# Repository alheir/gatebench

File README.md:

# GateBench

Educational FPGA lab board for the UPduino v3.1. Switches, LEDs, 7-segment display, VGA, R-2R DAC, ADC and WS2812 behind shift-register scan chains, with a Verilog BSP and worked examples.

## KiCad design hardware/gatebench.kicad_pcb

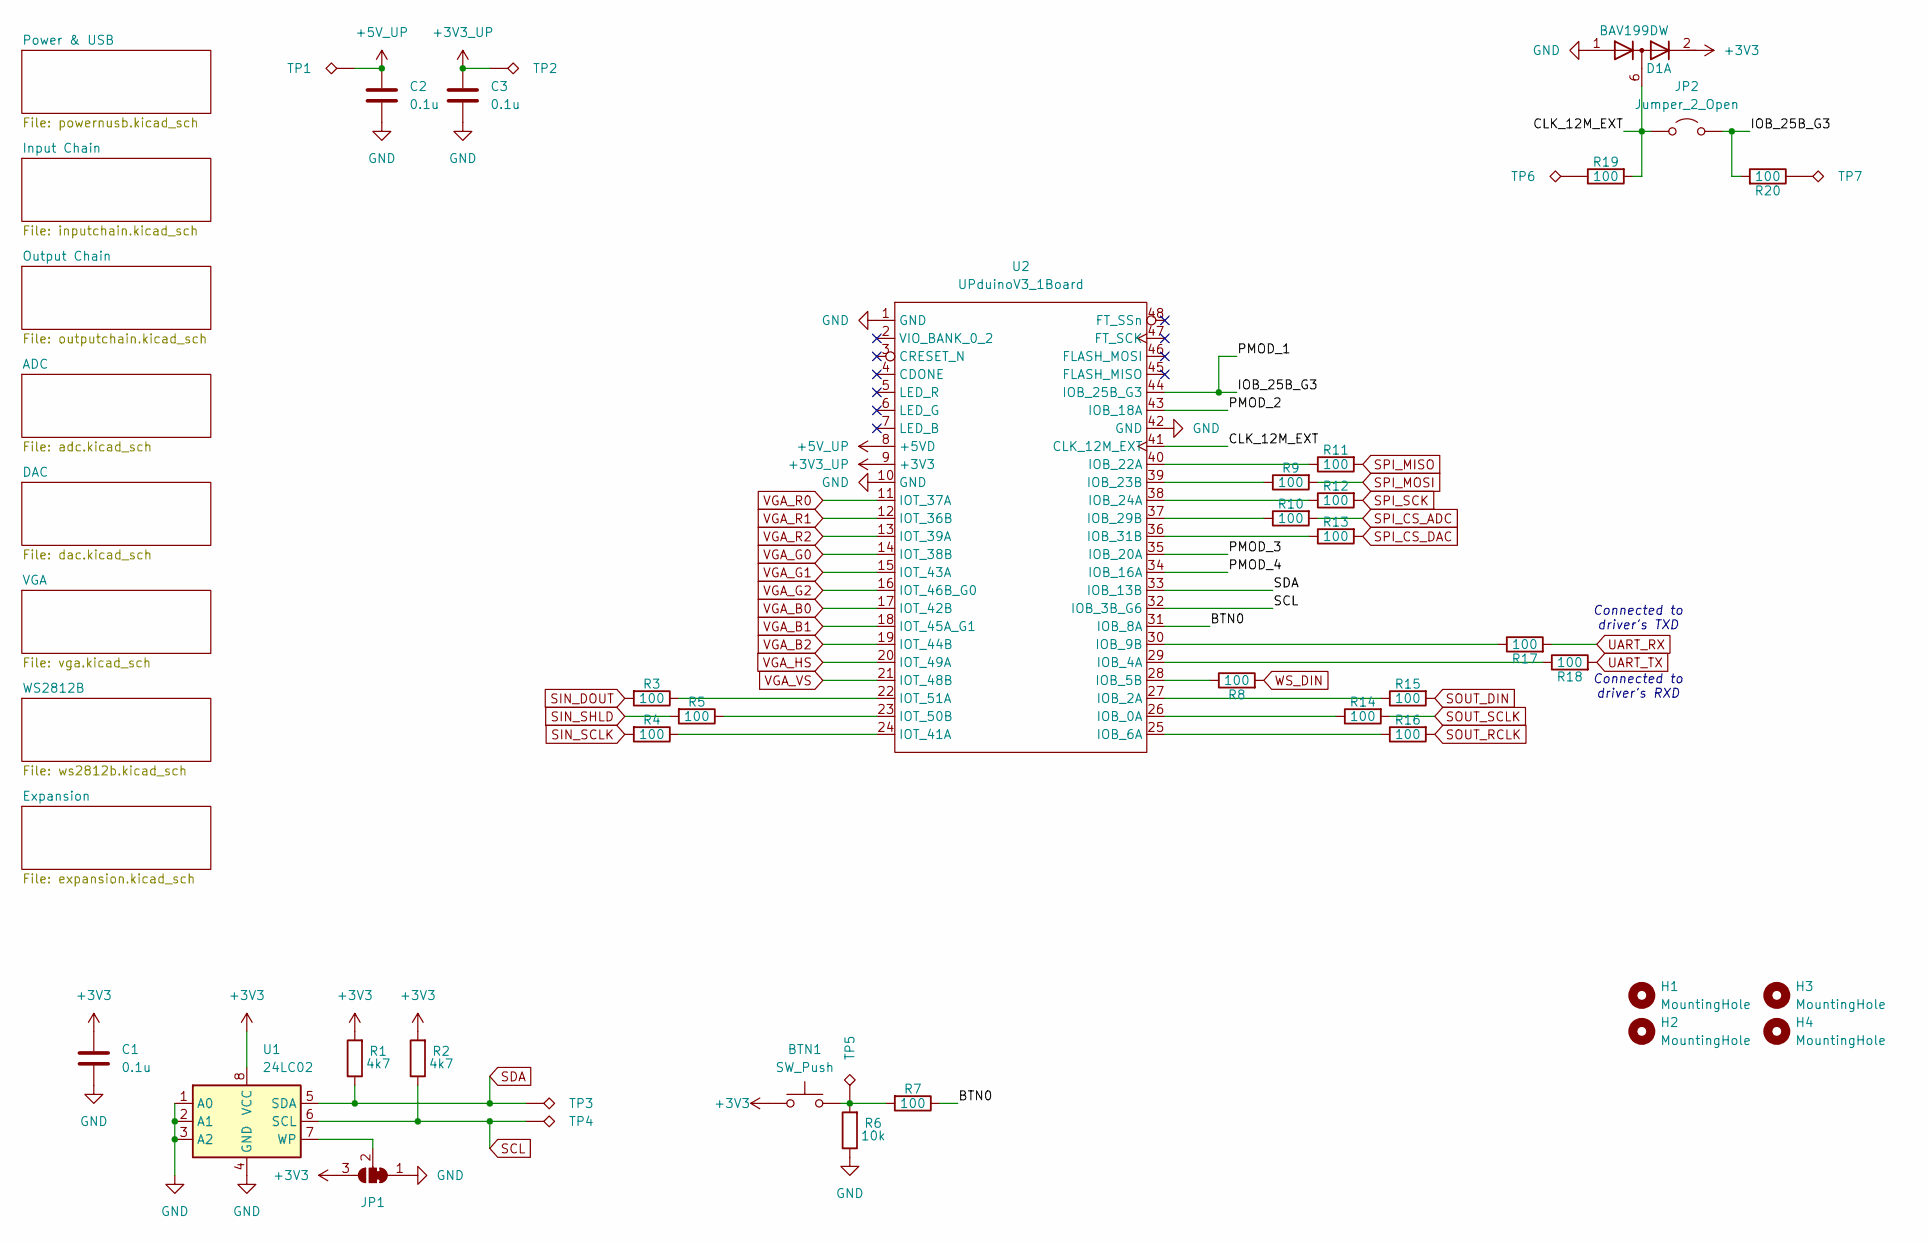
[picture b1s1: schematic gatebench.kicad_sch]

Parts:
BTN1: SW_Push; SW_PUSH_6mm_H8.5mm; JLCPCB C22397158
C1, C2, C3: 0.1u; C_0603_1608Metric_Pad1.08x0.95mm_HandSolder; JLCPCB C1705
D1: BAV199DW; SOT-363_SC-70-6
H1, H2, H3, H4: MountingHole; MountingHole_3.2mm_M3
JP1: SolderJumper_3_Bridged12; SolderJumper-3_P1.3mm_Bridged2Bar12_RoundedPad1.0x1.5mm_Num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
JP2: Jumper_2_Open
R1, R2: 4k7; R_0603_1608Metric; JLCPCB C22356621
R3, R4, R5, R7, R8, R9, R10, R11, R12, R13, R14, R15, R16, R17, R18, R19, R20: 100; R_0603_1608Metric; JLCPCB C22356621
R6: 10k; R_0603_1608Metric; JLCPCB C22356621
TP1, TP2, TP3, TP4, TP5, TP6, TP7: TestPoint_Alt; PinHeader_1x01_P2.54mm_Vertical
U1: 24LC02; SOIC-8_3.9x4.9mm_P1.27mm
U2: UPduinoV3_1Board; upduino_v3_1

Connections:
+3V3: BTN1.1, C1.1, D1.2 (K2), JP1.3 (B), R1.2, R2.2, U1.8 (VCC); also elsewhere on the board
+3V3_UP: C3.1, TP2.1 (1_1), U2.9 (+3V3); also elsewhere on the board
+5V_UP: C2.1, TP1.1 (1_1), U2.8 (+5VD); also elsewhere on the board
/BTN0: R7.1, U2.31 (IOB_8A)
/CLK_12M_EXT: D1.6 (K3A4), JP2.1 (A), R19.2, U2.41 (CLK_12M_EXT)
/IOB_25B_G3: JP2.2 (B), R20.2, U2.44 (IOB_25B_G3)
/PMOD_2: U2.43 (IOB_18A)
/PMOD_3: U2.35 (IOB_20A)
/PMOD_4: U2.34 (IOB_16A)
GND: C1.2, C2.2, C3.2, D1.1 (A1), JP1.1 (A), R6.1, U1.1 (A0), U1.2 (A1), U1.3 (A2), U1.4 (GND), U2.1 (GND), U2.10 (GND), U2.42 (GND); also elsewhere on the board
unnamed: BTN1.2, R6.2, R7.2, TP5.1 (1_1)
unnamed: JP1.2 (C), U1.7 (WP)
unnamed: R19.1, TP6.1 (1_1)
unnamed: R20.1, TP7.1 (1_1)
unnamed: R14.1, U2.26 (IOB_0A)
unnamed: R15.1, U2.27 (IOB_2A)
unnamed: R18.1, U2.29 (IOB_4A)
unnamed: R8.1, U2.28 (IOB_5B)
unnamed: R16.1, U2.25 (IOB_6A)
unnamed: R17.1, U2.30 (IOB_9B)
unnamed: R11.1, U2.40 (IOB_22A)
unnamed: R9.1, U2.39 (IOB_23B)
unnamed: R12.1, U2.38 (IOB_24A)
unnamed: R10.1, U2.37 (IOB_29B)
unnamed: R13.1, U2.36 (IOB_31B)
unnamed: R4.1, U2.24 (IOT_41A)
unnamed: R5.1, U2.23 (IOT_50B)
unnamed: R3.1, U2.22 (IOT_51A)
PMOD_7: R11.2; also elsewhere on the board
PMOD_8: R9.2; also elsewhere on the board
PMOD_9: R12.2; also elsewhere on the board
SCL: R2.1, TP4.1 (1_1), U1.6 (SCL), U2.32 (IOB_3B_G6); also elsewhere on the board
SDA: R1.1, TP3.1 (1_1), U1.5 (SDA), U2.33 (IOB_13B); also elsewhere on the board
SIN_DOUT: R3.2; also elsewhere on the board
SIN_SCLK: R4.2; also elsewhere on the board
SIN_SHLD: R5.2; also elsewhere on the board
SOUT_DIN: R15.2; also elsewhere on the board
SOUT_RCLK: R16.2; also elsewhere on the board
SOUT_SCLK: R14.2; also elsewhere on the board
SPI_CS_ADC: R10.2; also elsewhere on the board
SPI_CS_DAC: R13.2; also elsewhere on the board
UART_RX: R17.2; also elsewhere on the board
UART_TX: R18.2; also elsewhere on the board
VGA_B0: U2.17 (IOT_42B); also elsewhere on the board
VGA_B1: U2.18 (IOT_45A_G1); also elsewhere on the board
VGA_B2: U2.19 (IOT_44B); also elsewhere on the board
VGA_G0: U2.14 (IOT_38B); also elsewhere on the board
VGA_G1: U2.15 (IOT_43A); also elsewhere on the board
VGA_G2: U2.16 (IOT_46B_G0); also elsewhere on the board
VGA_HS: U2.20 (IOT_49A); also elsewhere on the board
VGA_R0: U2.11 (IOT_37A); also elsewhere on the board
VGA_R1: U2.12 (IOT_36B); also elsewhere on the board
VGA_R2: U2.13 (IOT_39A); also elsewhere on the board
VGA_VS: U2.21 (IOT_48B); also elsewhere on the board
WS_DIN: R8.2; also elsewhere on the board

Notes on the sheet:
Connected to driver's TXD
Connected to driver's RXD

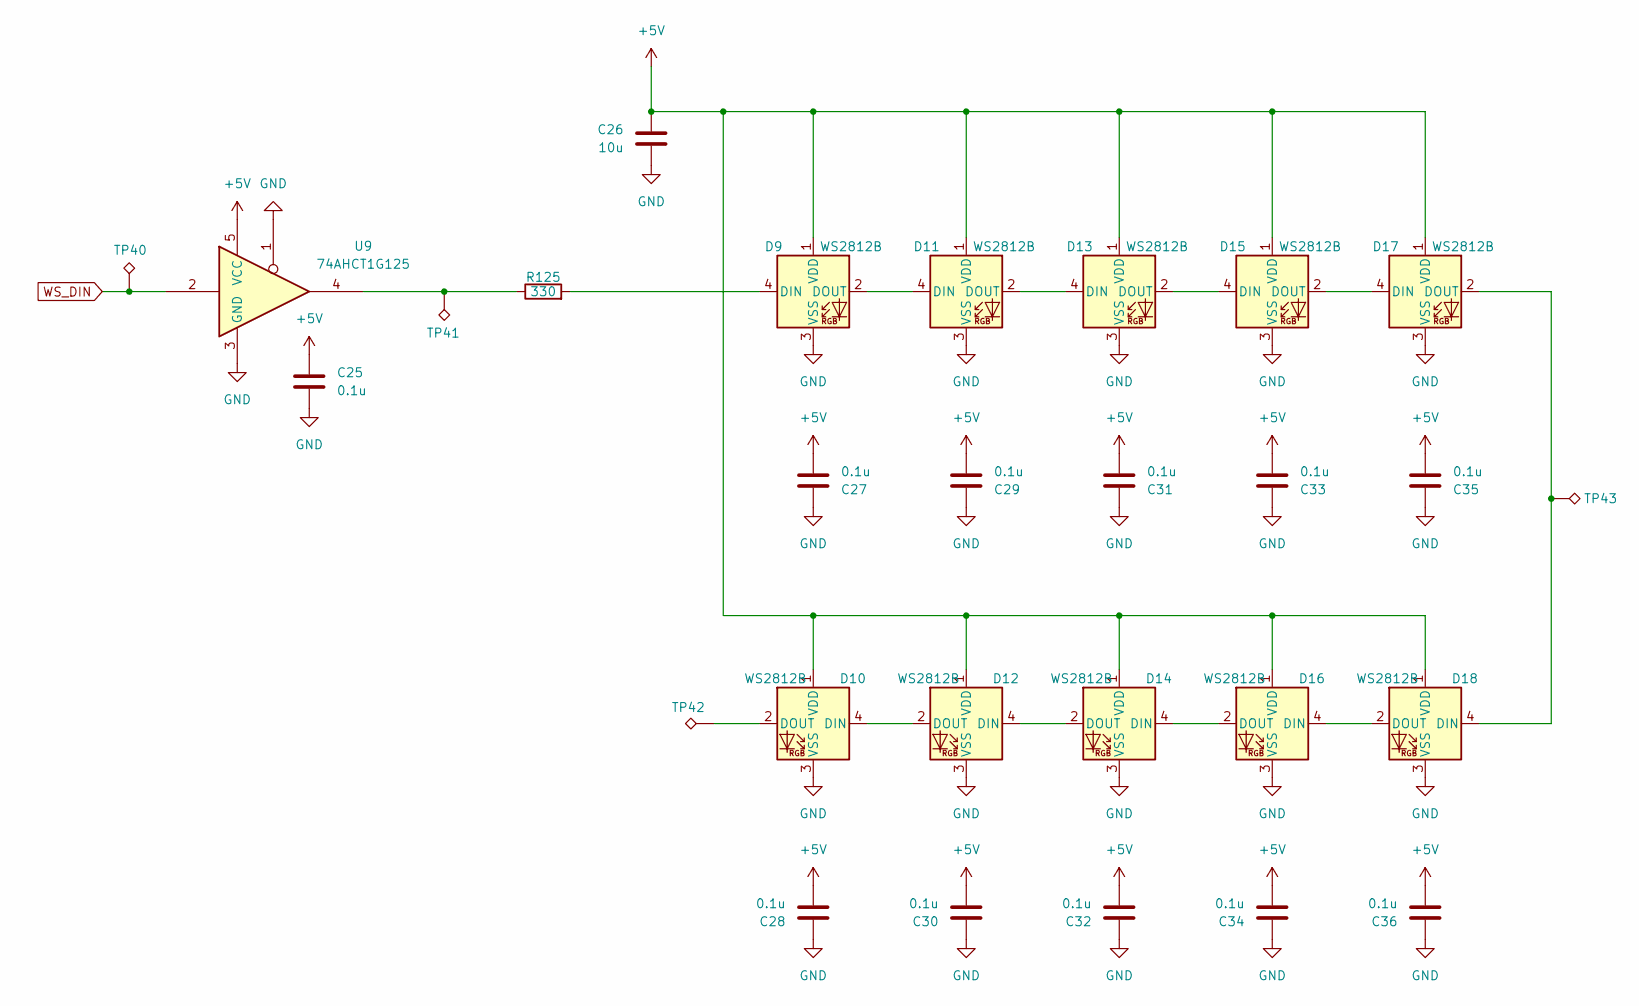
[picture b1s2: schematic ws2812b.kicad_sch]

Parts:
C25, C27, C28, C29, C30, C31, C32, C33, C34, C35, C36: 0.1u; C_0603_1608Metric_Pad1.08x0.95mm_HandSolder; JLCPCB C1705
C26: 10u; C_0603_1608Metric_Pad1.08x0.95mm_HandSolder; JLCPCB C1705
D9, D10, D11, D12, D13, D14, D15, D16, D17, D18: WS2812B; LED_WS2812B_PLCC4_5.0x5.0mm_P3.2mm; LCSC Part # C2843785
R125: 330; R_0603_1608Metric; JLCPCB C22356621
TP40, TP41, TP42, TP43: TestPoint_Alt; PinHeader_1x01_P2.54mm_Vertical
U9: 74AHCT1G125; SOT-23-5

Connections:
+5V: C25.1, C26.1, C27.2, C28.2, C29.2, C30.2, C31.2, C32.2, C33.2, C34.2, C35.2, C36.2, D9.1 (VDD), D10.1 (VDD), D11.1 (VDD), D12.1 (VDD), D13.1 (VDD), D14.1 (VDD), D15.1 (VDD), D16.1 (VDD), D17.1 (VDD), D18.1 (VDD), U9.5 (VCC); also elsewhere on the board
GND: C25.2, C26.2, C27.1, C28.1, C29.1, C30.1, C31.1, C32.1, C33.1, C34.1, C35.1, C36.1, D9.3 (VSS), D10.3 (VSS), D11.3 (VSS), D12.3 (VSS), D13.3 (VSS), D14.3 (VSS), D15.3 (VSS), D16.3 (VSS), D17.3 (VSS), D18.3 (VSS), U9.1, U9.3 (GND); also elsewhere on the board
unnamed: D9.4 (DIN), R125.2
unnamed: D10.4 (DIN), D12.2 (DOUT)
unnamed: D10.2 (DOUT), TP42.1 (1_1)
unnamed: D9.2 (DOUT), D11.4 (DIN)
unnamed: D11.2 (DOUT), D13.4 (DIN)
unnamed: D12.4 (DIN), D14.2 (DOUT)
unnamed: D13.2 (DOUT), D15.4 (DIN)
unnamed: D14.4 (DIN), D16.2 (DOUT)
unnamed: D15.2 (DOUT), D17.4 (DIN)
unnamed: D16.4 (DIN), D18.2 (DOUT)
unnamed: D17.2 (DOUT), D18.4 (DIN), TP43.1 (1_1)
unnamed: R125.1, TP41.1 (1_1), U9.4
WS_DIN: TP40.1 (1_1), U9.2; also elsewhere on the board

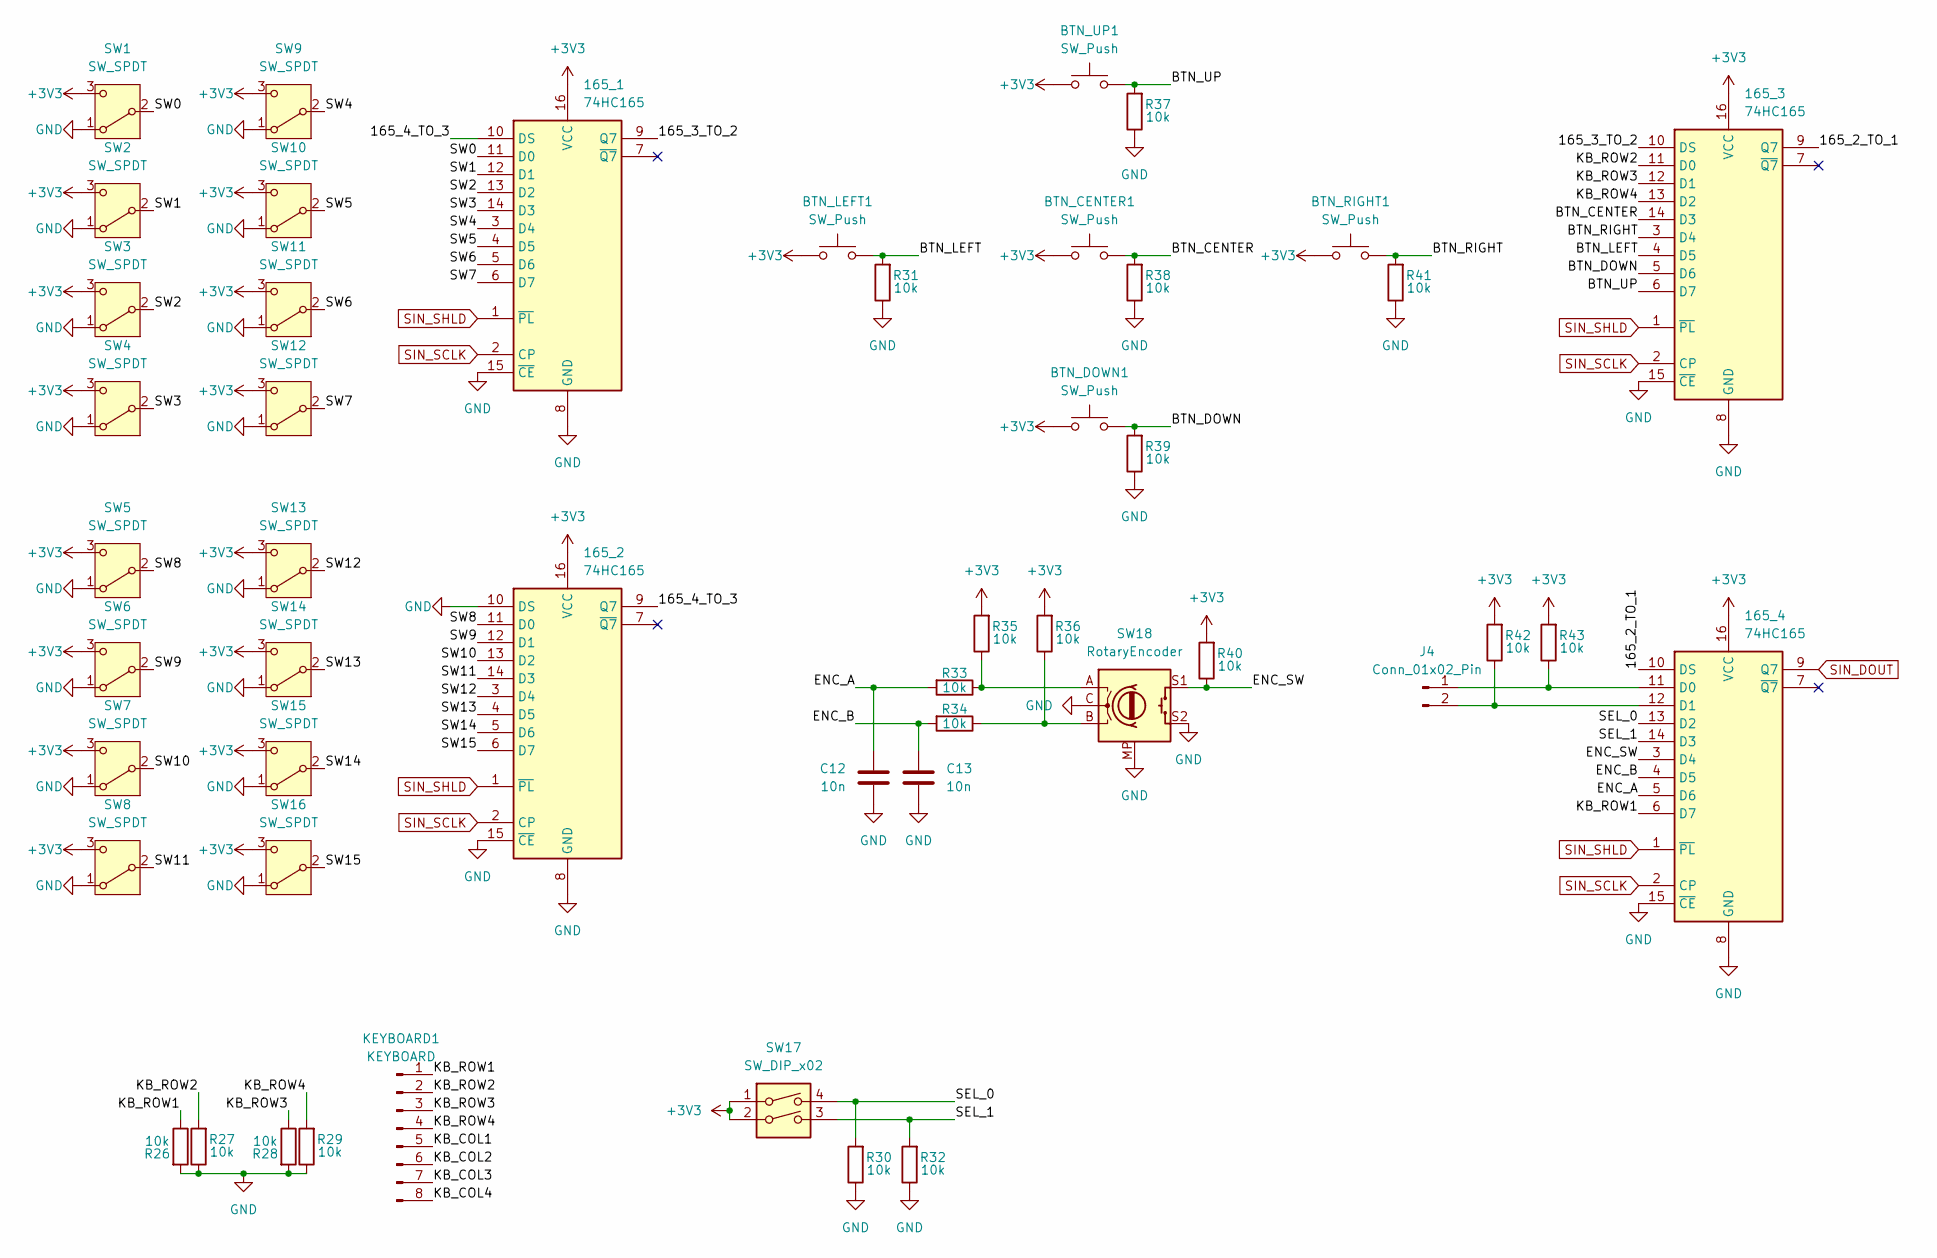
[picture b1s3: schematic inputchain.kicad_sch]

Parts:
165_1, 165_2, 165_3, 165_4: 74HC165; SO-16_3.9x9.9mm_P1.27mm
BTN_CENTER1: SW_Push; SW_PUSH_6mm_H8.5mm; JLCPCB C22397158
BTN_DOWN1: SW_Push; SW_PUSH_6mm_H8.5mm; JLCPCB C22397158
BTN_LEFT1: SW_Push; SW_PUSH_6mm_H8.5mm; JLCPCB C22397158
BTN_RIGHT1: SW_Push; SW_PUSH_6mm_H8.5mm; JLCPCB C22397158
BTN_UP1: SW_Push; SW_PUSH_6mm_H8.5mm; JLCPCB C22397158
C12, C13: 10n; C_0603_1608Metric_Pad1.08x0.95mm_HandSolder; JLCPCB C1705
J4: Conn_01x02_Pin; PinHeader_1x02_P2.54mm_Vertical
KEYBOARD1: KEYBOARD; PinHeader_1x08_P2.54mm_Horizontal
R26, R27, R28, R29, R30, R31, R32, R33, R34, R35, R36, R37, R38, R39, R40, R41, R42, R43: 10k; R_0603_1608Metric; JLCPCB C22356621
SW1, SW2, SW3, SW4, SW5, SW6, SW7, SW8, SW9, SW10, SW11, SW12, SW13, SW14, SW15, SW16: SW_SPDT; SW_Slide_SPDT_Straight_CK_OS102011MS2Q; JLCPCB C22435632
SW17: SW_DIP_x02; SW_DIP_SPSTx02_Slide_9.78x7.26mm_W7.62mm_P2.54mm; JLCPCB C5299503
SW18: RotaryEncoder; RotaryEncoder_Alps_EC11E-Switch_Vertical_H20mm

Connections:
+3V3: 165_1.16 (VCC), 165_2.16 (VCC), 165_3.16 (VCC), 165_4.16 (VCC), BTN_CENTER1.1, BTN_DOWN1.1, BTN_LEFT1.1, BTN_RIGHT1.1, BTN_UP1.1, R35.2, R36.2, R40.2, R42.2, R43.2, SW1.3 (C), SW2.3 (C), SW3.3 (C), SW4.3 (C), SW5.3 (C), SW6.3 (C), SW7.3 (C), SW8.3 (C), SW9.3 (C), SW10.3 (C), SW11.3 (C), SW12.3 (C), SW13.3 (C), SW14.3 (C), SW15.3 (C), SW16.3 (C), SW17.1, SW17.2; also elsewhere on the board
/Input Chain/165_2_TO_1: 165_3.9 (Q7), 165_4.10 (DS)
/Input Chain/165_3_TO_2: 165_1.9 (Q7), 165_3.10 (DS)
/Input Chain/165_4_TO_3: 165_1.10 (DS), 165_2.9 (Q7)
/Input Chain/BTN_CENTER: 165_3.14 (D3), BTN_CENTER1.2, R38.2
/Input Chain/BTN_DOWN: 165_3.5 (D6), BTN_DOWN1.2, R39.2
/Input Chain/BTN_LEFT: 165_3.4 (D5), BTN_LEFT1.2, R31.2
/Input Chain/BTN_RIGHT: 165_3.3 (D4), BTN_RIGHT1.2, R41.2
/Input Chain/BTN_UP: 165_3.6 (D7), BTN_UP1.2, R37.2
/Input Chain/ENC_A: 165_4.5 (D6), C12.1, R33.2
/Input Chain/ENC_B: 165_4.4 (D5), C13.1, R34.2
/Input Chain/ENC_SW: 165_4.3 (D4), R40.1, SW18.S1
/Input Chain/KB_COL1: KEYBOARD1.5
/Input Chain/KB_COL2: KEYBOARD1.6
/Input Chain/KB_COL3: KEYBOARD1.7
/Input Chain/KB_COL4: KEYBOARD1.8
/Input Chain/KB_ROW1: 165_4.6 (D7), KEYBOARD1.1, R26.1
/Input Chain/KB_ROW2: 165_3.11 (D0), KEYBOARD1.2, R27.2
/Input Chain/KB_ROW3: 165_3.12 (D1), KEYBOARD1.3, R28.1
/Input Chain/KB_ROW4: 165_3.13 (D2), KEYBOARD1.4, R29.2
/Input Chain/SEL_0: 165_4.13 (D2), R30.2, SW17.4
/Input Chain/SEL_1: 165_4.14 (D3), R32.2, SW17.3
/Input Chain/SW0: 165_1.11 (D0), SW1.2 (B)
/Input Chain/SW1: 165_1.12 (D1), SW2.2 (B)
/Input Chain/SW2: 165_1.13 (D2), SW3.2 (B)
/Input Chain/SW3: 165_1.14 (D3), SW4.2 (B)
/Input Chain/SW4: 165_1.3 (D4), SW9.2 (B)
/Input Chain/SW5: 165_1.4 (D5), SW10.2 (B)
/Input Chain/SW6: 165_1.5 (D6), SW11.2 (B)
/Input Chain/SW7: 165_1.6 (D7), SW12.2 (B)
/Input Chain/SW8: 165_2.11 (D0), SW5.2 (B)
/Input Chain/SW9: 165_2.12 (D1), SW6.2 (B)
/Input Chain/SW10: 165_2.13 (D2), SW7.2 (B)
/Input Chain/SW11: 165_2.14 (D3), SW8.2 (B)
/Input Chain/SW12: 165_2.3 (D4), SW13.2 (B)
/Input Chain/SW13: 165_2.4 (D5), SW14.2 (B)
/Input Chain/SW14: 165_2.5 (D6), SW15.2 (B)
/Input Chain/SW15: 165_2.6 (D7), SW16.2 (B)
GND: 165_1.8 (GND), 165_1.15 (~CE), 165_2.8 (GND), 165_2.10 (DS), 165_2.15 (~CE), 165_3.8 (GND), 165_3.15 (~CE), 165_4.8 (GND), 165_4.15 (~CE), C12.2, C13.2, R26.2, R27.1, R28.2, R29.1, R30.1, R31.1, R32.1, R37.1, R38.1, R39.1, R41.1, SW1.1 (A), SW2.1 (A), SW3.1 (A), SW4.1 (A), SW5.1 (A), SW6.1 (A), SW7.1 (A), SW8.1 (A), SW9.1 (A), SW10.1 (A), SW11.1 (A), SW12.1 (A), SW13.1 (A), SW14.1 (A), SW15.1 (A), SW16.1 (A), SW18.C, SW18.MP, SW18.S2; also elsewhere on the board
unnamed: 165_4.11 (D0), J4.1, R43.1
unnamed: 165_4.12 (D1), J4.2, R42.1
unnamed: R33.1, R35.1, SW18.A
unnamed: R34.1, R36.1, SW18.B
SIN_DOUT: 165_4.9 (Q7); also elsewhere on the board
SIN_SCLK: 165_1.2 (CP), 165_2.2 (CP), 165_3.2 (CP), 165_4.2 (CP); also elsewhere on the board
SIN_SHLD: 165_1.1 (~PL), 165_2.1 (~PL), 165_3.1 (~PL), 165_4.1 (~PL); also elsewhere on the board

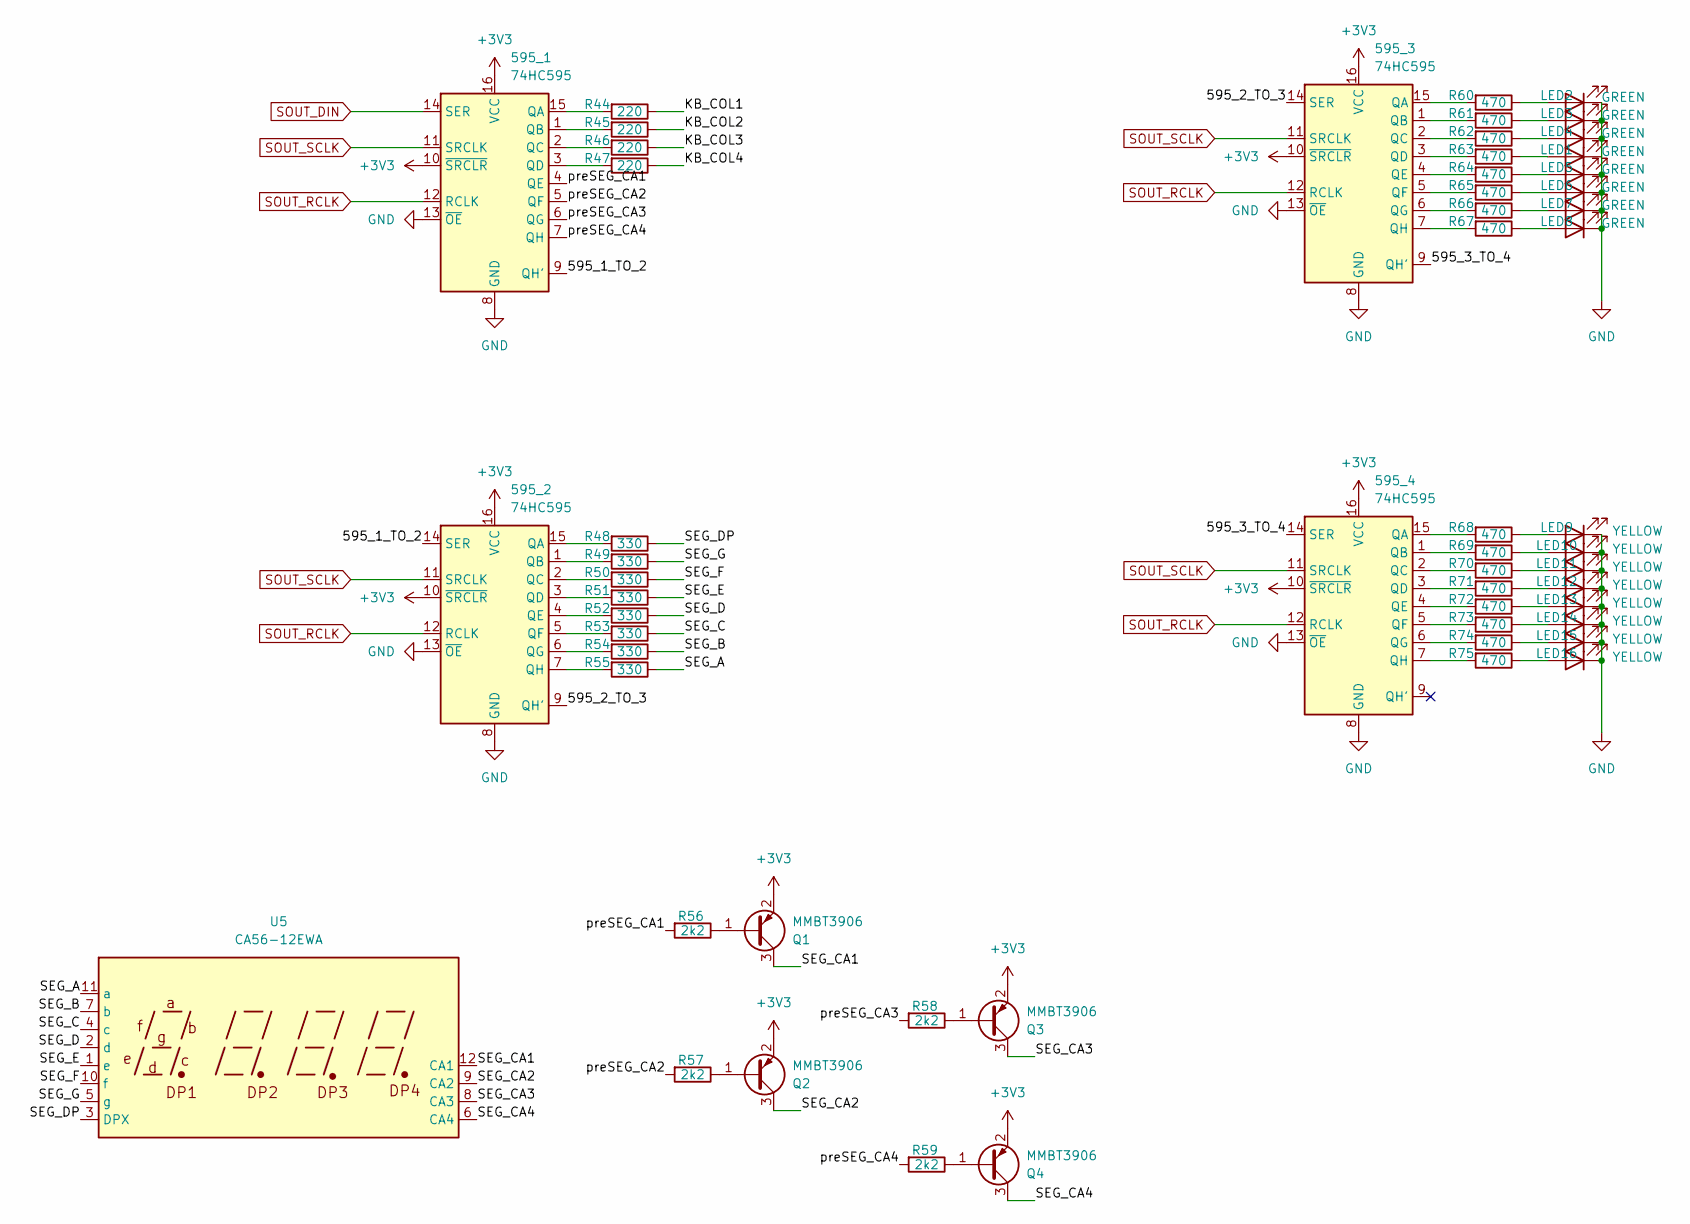
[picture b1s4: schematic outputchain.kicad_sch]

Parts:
595_1, 595_2, 595_3, 595_4: 74HC595; SOIC-16_3.9x9.9mm_P1.27mm
LED1, LED2, LED3, LED4, LED5, LED6, LED7, LED8: GREEN; LED_0603_1608Metric; LCSC Part # C12624
LED9, LED10, LED11, LED12, LED13, LED14, LED15, LED16: YELLOW; LED_0603_1608Metric; LCSC Part # C2287
Q1, Q2, Q3, Q4: MMBT3906; Nidec_Copal_CAS-120A
R44, R45, R46, R47: 220; R_0603_1608Metric; JLCPCB C22356621
R48, R49, R50, R51, R52, R53, R54, R55: 330; R_0603_1608Metric; JLCPCB C22356621
R56, R57, R58, R59: 2k2; R_0603_1608Metric; JLCPCB C22356621
R60, R61, R62, R63, R64, R65, R66, R67, R68, R69, R70, R71, R72, R73, R74, R75: 470; R_0603_1608Metric; JLCPCB C22356621
U5: CA56-12EWA

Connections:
+3V3: 595_1.10 (~SRCLR), 595_1.16 (VCC), 595_2.10 (~SRCLR), 595_2.16 (VCC), 595_3.10 (~SRCLR), 595_3.16 (VCC), 595_4.10 (~SRCLR), 595_4.16 (VCC), Q1.2 (E), Q2.2 (E), Q3.2 (E), Q4.2 (E); also elsewhere on the board
/Output Chain/595_1_TO_2: 595_1.9 (QH'), 595_2.14 (SER)
/Output Chain/595_2_TO_3: 595_2.9 (QH'), 595_3.14 (SER)
/Output Chain/595_3_TO_4: 595_3.9 (QH'), 595_4.14 (SER)
/Output Chain/KB_COL1: R44.1
/Output Chain/KB_COL2: R45.1
/Output Chain/KB_COL3: R46.1
/Output Chain/KB_COL4: R47.1
/Output Chain/SEG_A: R55.1, U5.11 (a)
/Output Chain/SEG_B: R54.1, U5.7 (b)
/Output Chain/SEG_C: R53.1, U5.4 (c)
/Output Chain/SEG_CA1: Q1.3 (C), U5.12 (CA1)
/Output Chain/SEG_CA2: Q2.3 (C), U5.9 (CA2)
/Output Chain/SEG_CA3: Q3.3 (C), U5.8 (CA3)
/Output Chain/SEG_CA4: Q4.3 (C), U5.6 (CA4)
/Output Chain/SEG_D: R52.1, U5.2 (d)
/Output Chain/SEG_DP: R48.1, U5.3 (DPX)
/Output Chain/SEG_E: R51.1, U5.1 (e)
/Output Chain/SEG_F: R50.1, U5.10 (f)
/Output Chain/SEG_G: R49.1, U5.5 (g)
/Output Chain/preSEG_CA1: 595_1.4 (QE), R56.2
/Output Chain/preSEG_CA2: 595_1.5 (QF), R57.2
/Output Chain/preSEG_CA3: 595_1.6 (QG), R58.2
/Output Chain/preSEG_CA4: 595_1.7 (QH), R59.2
GND: 595_1.8 (GND), 595_1.13 (~OE), 595_2.8 (GND), 595_2.13 (~OE), 595_3.8 (GND), 595_3.13 (~OE), 595_4.8 (GND), 595_4.13 (~OE), LED2.1 (K), LED3.1 (K), LED4.1 (K), LED5.1 (K), LED6.1 (K), LED7.1 (K), LED8.1 (K), LED9.1 (K), LED10.1 (K), LED11.1 (K), LED12.1 (K), LED13.1 (K), LED14.1 (K), LED15.1 (K), LED16.1 (K); also elsewhere on the board
unnamed: 595_1.15 (QA), R44.2
unnamed: 595_1.1 (QB), R45.2
unnamed: 595_1.2 (QC), R46.2
unnamed: 595_1.3 (QD), R47.2
unnamed: 595_2.15 (QA), R48.2
unnamed: 595_2.1 (QB), R49.2
unnamed: 595_2.2 (QC), R50.2
unnamed: 595_2.3 (QD), R51.2
unnamed: 595_2.4 (QE), R52.2
unnamed: 595_2.5 (QF), R53.2
unnamed: 595_2.6 (QG), R54.2
unnamed: 595_2.7 (QH), R55.2
unnamed: 595_3.15 (QA), R60.2
unnamed: 595_3.1 (QB), R61.2
unnamed: 595_3.2 (QC), R62.2
unnamed: 595_3.3 (QD), R63.2
unnamed: 595_3.4 (QE), R64.2
unnamed: 595_3.5 (QF), R65.2
unnamed: 595_3.6 (QG), R66.2
unnamed: 595_3.7 (QH), R67.2
unnamed: 595_4.15 (QA), R68.2
unnamed: 595_4.1 (QB), R69.2
unnamed: 595_4.2 (QC), R70.2
unnamed: 595_4.3 (QD), R71.2
unnamed: 595_4.4 (QE), R72.2
unnamed: 595_4.5 (QF), R73.2
unnamed: 595_4.6 (QG), R74.2
unnamed: 595_4.7 (QH), R75.2
unnamed: LED2.2 (A), R60.1
unnamed: LED3.2 (A), R61.1
unnamed: LED4.2 (A), R62.1
unnamed: LED5.2 (A), R64.1
unnamed: LED6.2 (A), R65.1
unnamed: LED7.2 (A), R66.1
unnamed: LED8.2 (A), R67.1
unnamed: LED9.2 (A), R68.1
unnamed: LED10.2 (A), R69.1
unnamed: LED11.2 (A), R70.1
unnamed: LED12.2 (A), R71.1
unnamed: LED13.2 (A), R72.1
unnamed: LED14.2 (A), R73.1
unnamed: LED15.2 (A), R74.1
unnamed: LED16.2 (A), R75.1
unnamed: Q1.1 (B), R56.1
unnamed: Q2.1 (B), R57.1
unnamed: Q3.1 (B), R58.1
unnamed: Q4.1 (B), R59.1
SOUT_DIN: 595_1.14 (SER); also elsewhere on the board
SOUT_RCLK: 595_1.12 (RCLK), 595_2.12 (RCLK), 595_3.12 (RCLK), 595_4.12 (RCLK); also elsewhere on the board
SOUT_SCLK: 595_1.11 (SRCLK), 595_2.11 (SRCLK), 595_3.11 (SRCLK), 595_4.11 (SRCLK); also elsewhere on the board

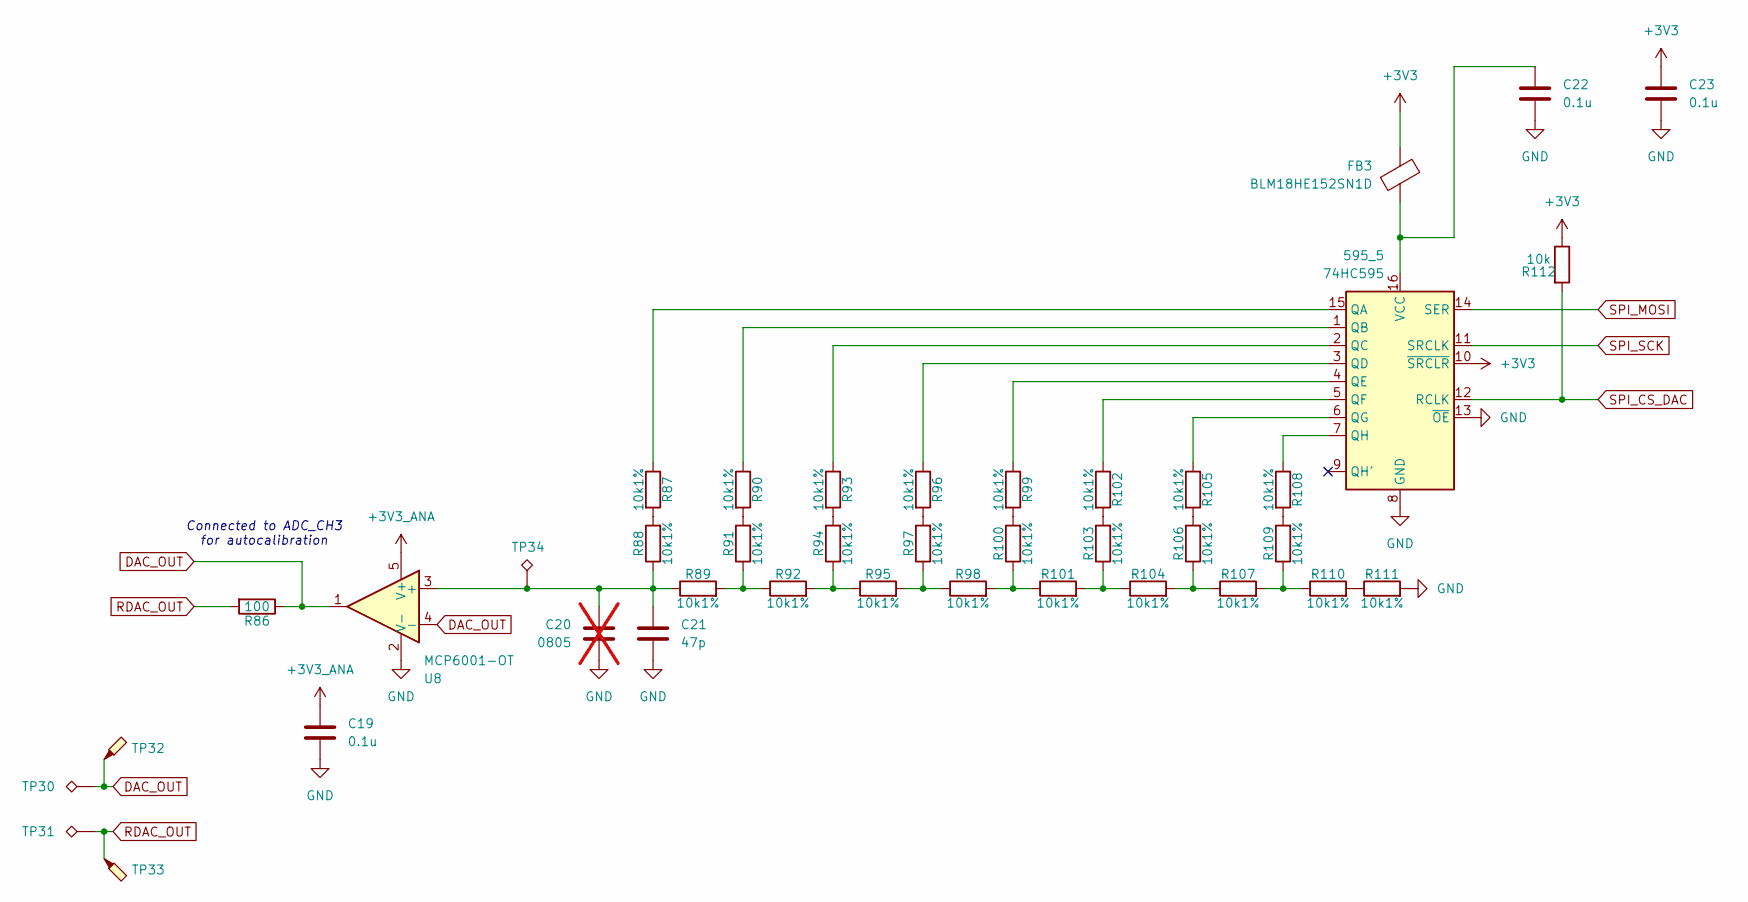
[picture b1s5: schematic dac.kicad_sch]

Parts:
595_5: 74HC595; SOIC-16_3.9x9.9mm_P1.27mm
C19, C22, C23: 0.1u; C_0603_1608Metric_Pad1.08x0.95mm_HandSolder; JLCPCB C1705
C20: 0805; C_0603_1608Metric_Pad1.08x0.95mm_HandSolder; JLCPCB C1705; not fitted
C21: 47p; C_0603_1608Metric_Pad1.08x0.95mm_HandSolder; JLCPCB C1705
FB3: BLM18HE152SN1D; L_0603_1608Metric; LCSC Part # C82155
R86: 100; R_0603_1608Metric; JLCPCB C22356621
R87, R88, R89, R90, R91, R92, R93, R94, R95, R96, R97, R98, R99, R100, R101, R102, R103, R104, R105, R106, R107, R108, R109, R110, R111: 10k1%; R_0603_1608Metric; JLCPCB C22356621
R112: 10k; R_0603_1608Metric; JLCPCB C22356621
TP30, TP31, TP34: TestPoint_Alt; PinHeader_1x01_P2.54mm_Vertical
TP32, TP33: TestPoint_Probe; TestPoint_Loop_D2.60mm_Drill0.9mm_Beaded
U8: MCP6001-OT; SOT-23-5

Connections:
+3V3: 595_5.10 (~SRCLR), C23.1, FB3.2, R112.1; also elsewhere on the board
+3V3_ANA: C19.1, U8.5 (V+); also elsewhere on the board
DAC_OUT: R86.1, TP30.1 (1_1), TP32.1 (1_1), U8.1, U8.4 (-); also elsewhere on the board
GND: 595_5.8 (GND), 595_5.13 (~OE), C19.2, C20.2, C21.2, C22.2, C23.2, R111.2, U8.2 (V-); also elsewhere on the board
unnamed: 595_5.15 (QA), R87.1
unnamed: 595_5.1 (QB), R90.1
unnamed: 595_5.2 (QC), R93.1
unnamed: 595_5.3 (QD), R96.1
unnamed: 595_5.4 (QE), R99.1
unnamed: 595_5.5 (QF), R102.1
unnamed: 595_5.6 (QG), R105.1
unnamed: 595_5.7 (QH), R108.1
unnamed: 595_5.16 (VCC), C22.1, FB3.1
unnamed: R87.2, R88.2
unnamed: R89.2, R91.1, R92.1
unnamed: R90.2, R91.2
unnamed: R92.2, R94.1, R95.1
unnamed: R93.2, R94.2
unnamed: R95.2, R97.1, R98.1
unnamed: R96.2, R97.2
unnamed: R98.2, R100.1, R101.1
unnamed: R99.2, R100.2
unnamed: R101.2, R103.1, R104.1
unnamed: R102.2, R103.2
unnamed: R104.2, R106.1, R107.1
unnamed: R105.2, R106.2
unnamed: R107.2, R109.1, R110.1
unnamed: R108.2, R109.2
unnamed: R110.2, R111.1
unnamed: C20.1, C21.1, R88.1, R89.1, TP34.1 (1_1), U8.3 (+)
PMOD_8: 595_5.14 (SER); also elsewhere on the board
PMOD_9: 595_5.11 (SRCLK); also elsewhere on the board
RDAC_OUT: R86.2, TP31.1 (1_1), TP33.1 (1_1)
SPI_CS_DAC: 595_5.12 (RCLK), R112.2; also elsewhere on the board

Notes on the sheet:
Connected to ADC_CH3 for autocalibration

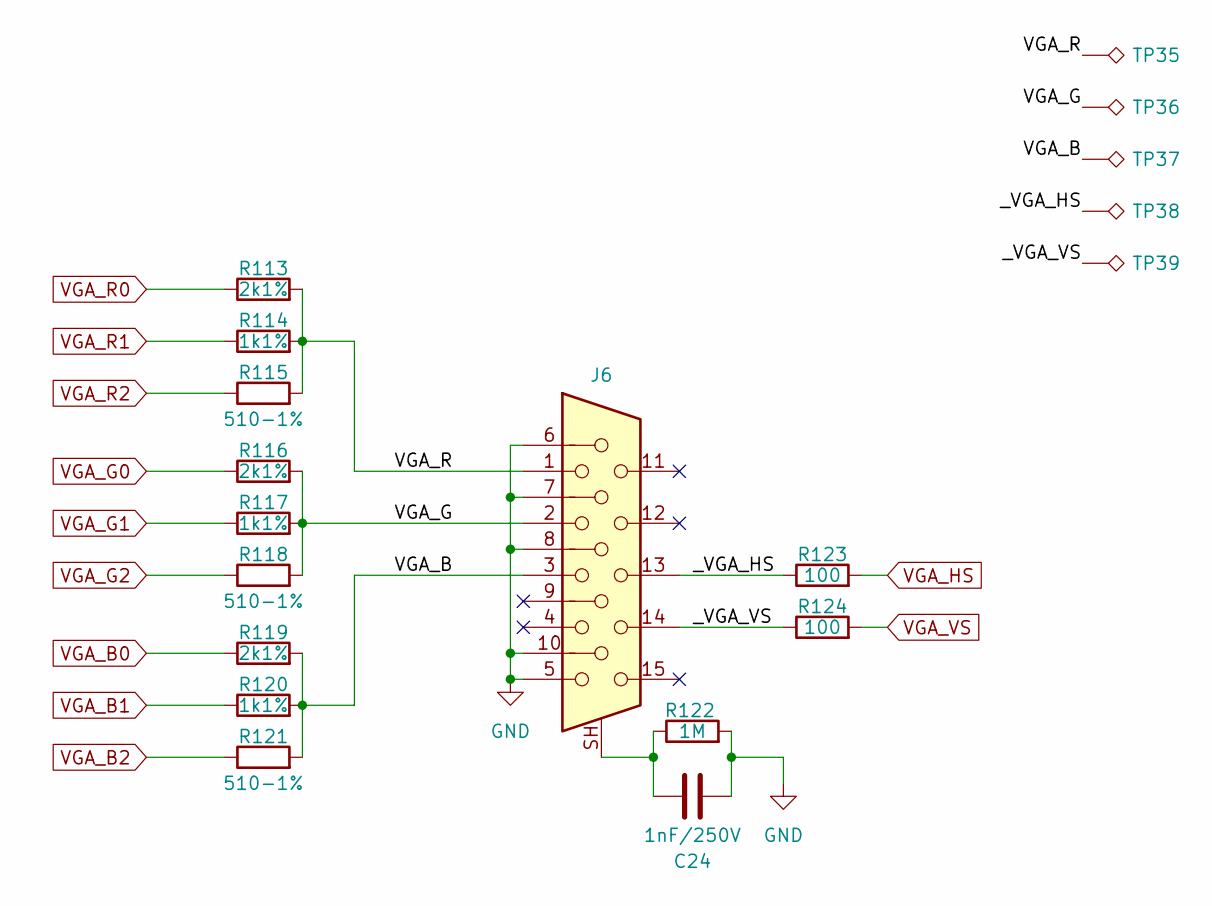
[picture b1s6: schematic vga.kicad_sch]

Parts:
C24: 1nF/250V; C_0603_1608Metric_Pad1.08x0.95mm_HandSolder; JLCPCB C277510
J6: DE15_Socket_HighDensity_MountingHoles; DSUB-15-HD_Socket_Horizontal_P2.29x2.54mm_EdgePinOffset8.35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; LCSC Part # C138387
R113, R116, R119: 2k1%; R_0603_1608Metric; JLCPCB C22356621
R114, R117, R120: 1k1%; R_0603_1608Metric; JLCPCB C22356621
R115, R118, R121: 510-1%; R_0603_1608Metric; JLCPCB C22356621
R122: 1M; R_0603_1608Metric; JLCPCB C22356623
R123, R124: 100; R_0603_1608Metric; JLCPCB C22356621
TP35, TP36, TP37, TP38, TP39: TestPoint_Alt; PinHeader_1x01_P2.54mm_Vertical

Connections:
/VGA/VGA_B: J6.3, R119.2, R120.2, R121.2, TP37.1 (1_1)
/VGA/VGA_G: J6.2, R116.2, R117.2, R118.2, TP36.1 (1_1)
/VGA/VGA_R: J6.1, R113.2, R114.2, R115.2, TP35.1 (1_1)
/VGA/_VGA_HS: J6.13, R123.1, TP38.1 (1_1)
/VGA/_VGA_VS: J6.14, R124.1, TP39.1 (1_1)
GND: C24.1, J6.5, J6.6, J6.7, J6.8, J6.10, R122.2; also elsewhere on the board
unnamed: C24.2, J6.SH, R122.1
VGA_B0: R119.1; also elsewhere on the board
VGA_B1: R120.1; also elsewhere on the board
VGA_B2: R121.1; also elsewhere on the board
VGA_G0: R116.1; also elsewhere on the board
VGA_G1: R117.1; also elsewhere on the board
VGA_G2: R118.1; also elsewhere on the board
VGA_HS: R123.2; also elsewhere on the board
VGA_R0: R113.1; also elsewhere on the board
VGA_R1: R114.1; also elsewhere on the board
VGA_R2: R115.1; also elsewhere on the board
VGA_VS: R124.2; also elsewhere on the board
